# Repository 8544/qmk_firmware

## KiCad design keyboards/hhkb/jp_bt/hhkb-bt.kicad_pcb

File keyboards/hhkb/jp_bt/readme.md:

HHKB-BT Alternate Controller
===

An alternative controler for the HHKB-BT designed by 8544.

Note: No Bluetooth support!

Keyboard Maintainer: 8544
Hardware Supported: HHKB-BT with Alternate Controller

Make example for this keyboard (after setting up your build environment):

    qmk complie hhkb/jp-bt:default

See [build environment setup](https://docs.qmk.fm/#/getting_started_build_tools) then the [make instructions](https://docs.qmk.fm/#/getting_started_make_guide) for more information.

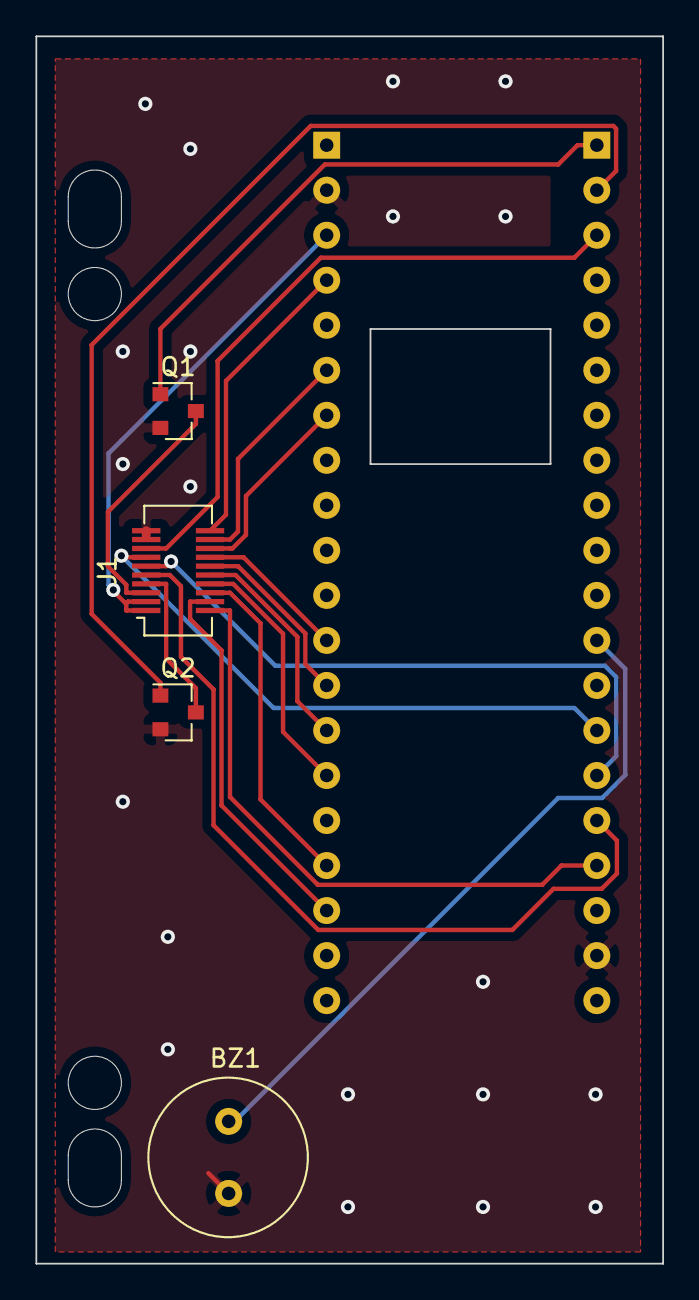
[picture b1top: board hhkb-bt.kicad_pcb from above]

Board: 2 copper layers, 35.4 x 69.2 mm, 5 parts (1 on the bottom side), 21 nets.

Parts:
BZ1: Buzzer; 9042 Buzzer
J1: Conn_02x10_Counter_Clockwise; Hirose_DF12_DF12C3.0-20DS-0.5V_2x10_P0.50mm_Vertical
J2: Conn_02x20_Counter_Clockwise; WeAct BlackPill
Q1, Q2: DTC123J; SOT-23

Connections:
+3V3: J1.1, J1.2, J2.38
GND: BZ1.2, J1.9, J1.10, J2.19, J2.39, Q1.2, Q2.2
unnamed: BZ1.1, J2.12
unnamed: J1.3, Q1.3
unnamed: J1.4, Q2.3
unnamed: J1.5, J2.16
unnamed: J1.6, J2.15
unnamed: J1.7, J2.14
unnamed: J1.8, J2.3
unnamed: J1.11, J2.17
unnamed: J1.12, J2.23
unnamed: J1.13, J2.24
unnamed: J1.14, J2.26
unnamed: J1.15, J2.27
unnamed: J1.16, J2.28
unnamed: J1.17, J2.29
unnamed: J1.18, J2.34
unnamed: J1.19, J2.35
unnamed: J1.20, J2.37
unnamed: J2.1, Q1.1
unnamed: J2.2, Q2.1

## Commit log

2024-02-05 feat: add hhkb/jp_bt keyboard
2024-02-05 docs: add schema
2024-02-05 fix: wait 10ms for each item in buffer
    workaround for broken Mod-Taps
2024-02-05 tapping force hold
2024-02-05 migrate to latest qmk
